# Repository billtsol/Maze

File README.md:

# Maze-Solving Robot

This project demonstrates how to use an Arduino board, IR sensors, and a motor driver shield to create a maze-solving robot. The robot is designed to navigate mazes by detecting, using sensors to make decisions at intersections.

## Requirements

To build this project, you will need the following components:

- ESP32 DevKit-S3
- IR sensors
- Motor driver shield
- Wheels and motors
- Jumper wires
- Battery pack
- Chassis
- Optional: Raspberry Pi (for additional functionality like 3D mapping and communication with a server)

## Circuit Diagram

## PCB

## Code

The code for this project is available in the `Maze.ino` file.

## Advanced Features

1. **Increased Size and Payload Capacity**: The robot's size can be increased to carry larger loads. This allows the robot to be used for more demanding applications, such as transporting packages or tools in industrial environments.

2. **Improved Navigation in Challenging Terrain**: The robot can be upgraded with enhanced drive systems to handle rough terrain. This feature enables the robot to navigate through more difficult environments, making it suitable for outdoor and emergency response applications.

3. **3D Mapping with LiDAR**: Adding LiDAR sensors to the robot allows it to create detailed 3D maps of its surroundings. This improves its maze-solving capabilities and makes it more versatile for tasks like underground exploration or hazardous area inspections. You can integrate LiDAR with software like ROS (Robot Operating System) and SLAM algorithms to create and visualize the 3D maps.

4. **Communication with Server using Raspberry Pi**: The robot can be connected to a server via a Raspberry Pi, enabling remote monitoring and control. This feature allows for real-time updates on the robot's progress through the maze and the ability to send and receive commands.

## Final Images

- Final pcb

- Final Mazo robot

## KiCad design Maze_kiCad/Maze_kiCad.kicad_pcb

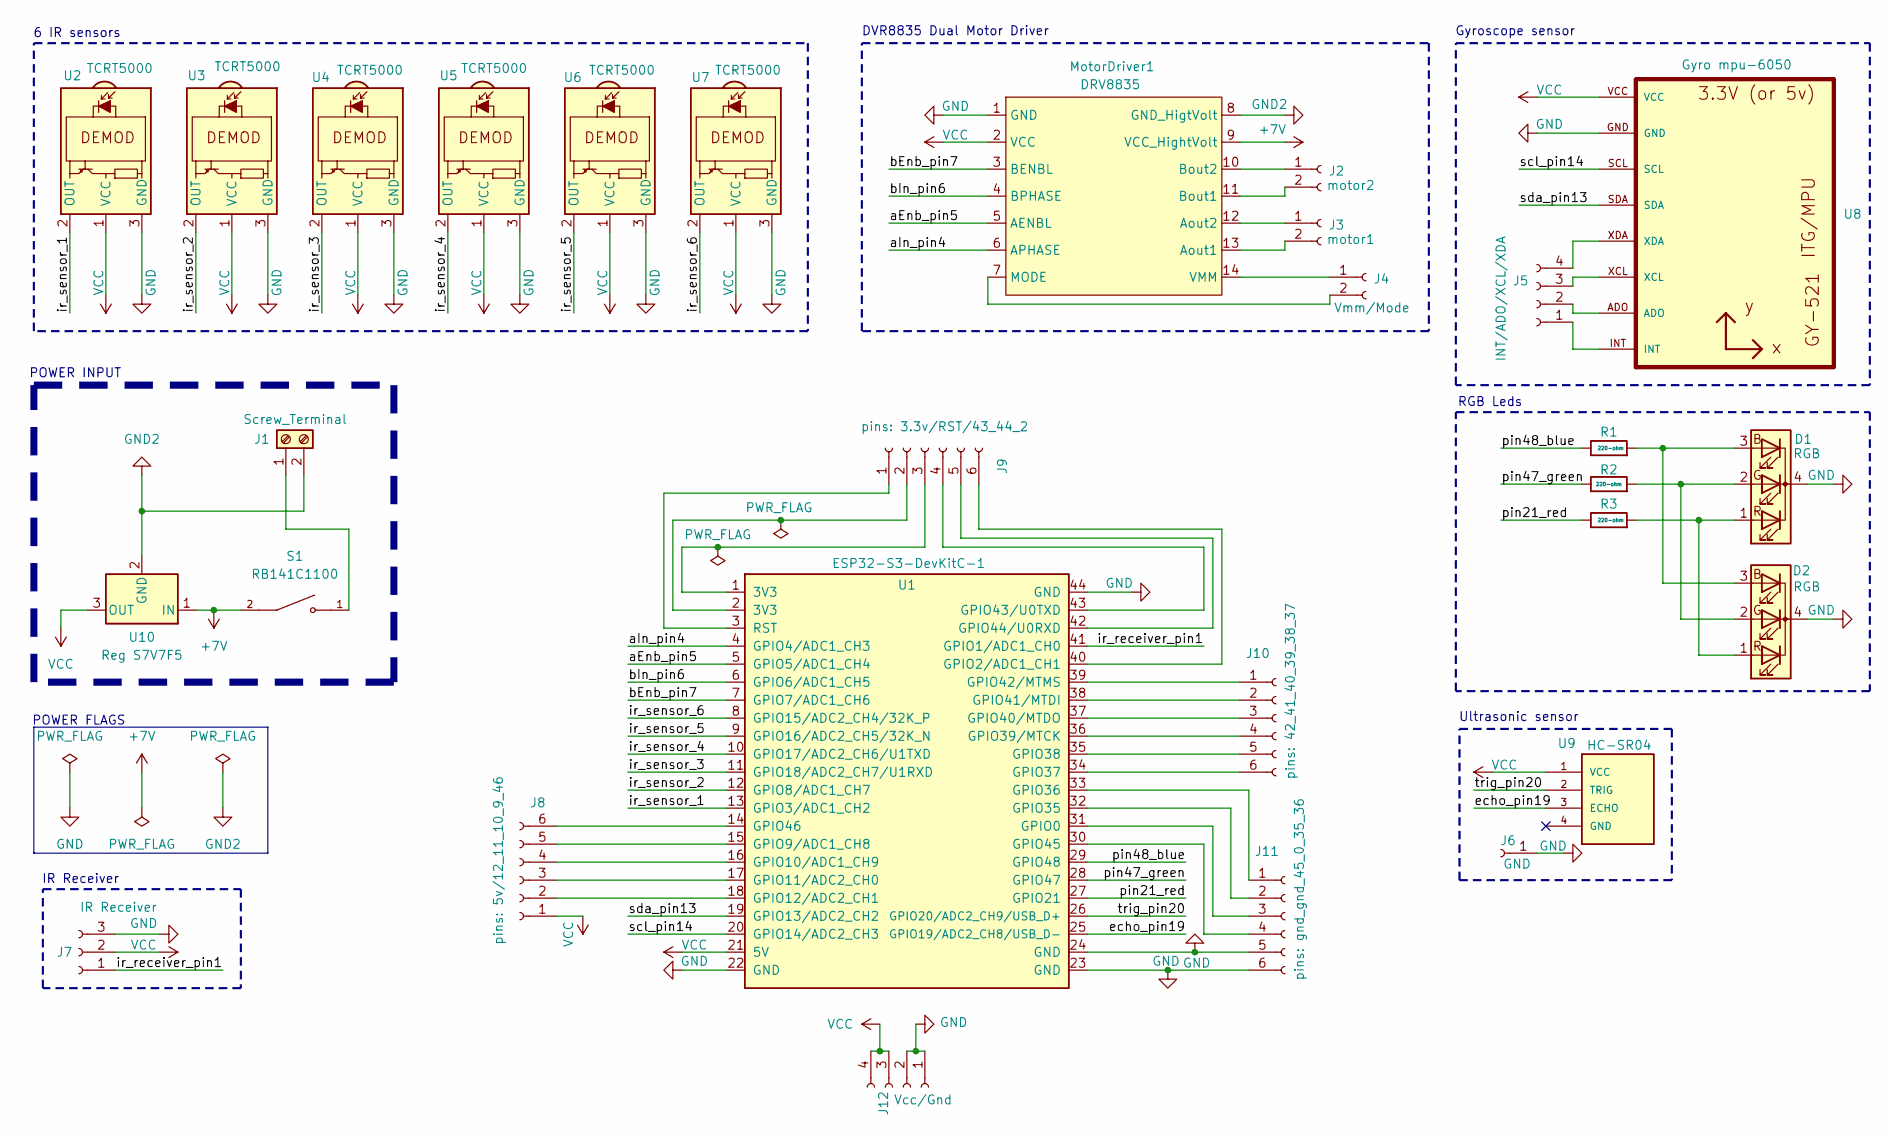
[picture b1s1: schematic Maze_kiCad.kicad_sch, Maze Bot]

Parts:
D1, D2: RGB; LED_D5.0mm-4_RGB_Staggered_Pins
J1: Screw_Terminal; TerminalBlock_Phoenix_MKDS-1,5-2_1x02_P5.00mm_Horizontal
J2: motor2; PinSocket_1x02_P2.54mm_Vertical
J3: motor1; PinSocket_1x02_P2.54mm_Vertical
J4: Vmm/Mode; PinSocket_1x02_P2.54mm_Vertical
J5: INT/ADO/XCL/XDA; PinSocket_1x04_P2.54mm_Vertical
J6: GND; PinSocket_1x01_P2.54mm_Vertical
J7: IR Receiver; PinSocket_1x03_P2.54mm_Vertical
J8: pins: 5v/12_11_10_9_46; PinSocket_1x06_P2.54mm_Vertical
J9: pins: 3.3v/RST/43_44_2; PinSocket_1x06_P2.54mm_Vertical
J10: pins: 42_41_40_39_38_37; PinSocket_1x06_P2.54mm_Vertical
J11: pins: gnd_gnd_45_0_35_36; PinSocket_1x06_P2.54mm_Vertical
J12: Vcc/Gnd; PinSocket_1x04_P2.54mm_Vertical
MotorDriver1: DRV8835; drv8835
R1, R2, R3: 220-ohm; R_Axial_DIN0204_L3.6mm_D1.6mm_P7.62mm_Horizontal
S1: RB141C1100; SW_RB141C1100; PARTREV C
U1: ESP32-S3-DevKitC-1; ESP32-S2-DevKitC-1
U2, U3, U4, U5, U6, U7: TCRT5000; Vishay_MINICAST-3Pin
U8: Gyro mpu-6050; GY-521
U9: HC-SR04; XCVR_HC-SR04
U10: Reg S7V7F5; PinSocket_1x03_P2.54mm_Vertical

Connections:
+7V: MotorDriver1.9 (VCC_HightVolt), S1.2, U10.1 (IN)
/aEnb_pin5: MotorDriver1.5 (AENBL), U1.5 (GPIO5/ADC1_CH4)
/aIn_pin4: MotorDriver1.6 (APHASE), U1.4 (GPIO4/ADC1_CH3)
/bEnb_pin7: MotorDriver1.3 (BENBL), U1.7 (GPIO7/ADC1_CH6)
/bIn_pin6: MotorDriver1.4 (BPHASE), U1.6 (GPIO6/ADC1_CH5)
/echo_pin19: U1.25 (GPIO19/ADC2_CH8/USB_D-), U9.3 (ECHO)
/ir_receiver_pin1: J7.1, U1.41 (GPIO1/ADC1_CH0)
/ir_sensor_1: U1.13 (GPIO3/ADC1_CH2), U2.2 (OUT)
/ir_sensor_2: U1.12 (GPIO8/ADC1_CH7), U3.2 (OUT)
/ir_sensor_3: U1.11 (GPIO18/ADC2_CH7/U1RXD), U4.2 (OUT)
/ir_sensor_4: U1.10 (GPIO17/ADC2_CH6/U1TXD), U5.2 (OUT)
/ir_sensor_5: U1.9 (GPIO16/ADC2_CH5/32K_N), U6.2 (OUT)
/ir_sensor_6: U1.8 (GPIO15/ADC2_CH4/32K_P), U7.2 (OUT)
/pin21_red: R3.1, U1.27 (GPIO21)
/pin47_green: R2.1, U1.28 (GPIO47)
/pin48_blue: R1.1, U1.29 (GPIO48)
/scl_pin14: U1.20 (GPIO14/ADC2_CH3), U8.SCL
/sda_pin13: U1.19 (GPIO13/ADC2_CH2), U8.SDA
/trig_pin20: U1.26 (GPIO20/ADC2_CH9/USB_D+), U9.2 (TRIG)
GND: D1.4 (K), D2.4 (K), J6.1, J7.3, J11.5, J11.6, J12.1, J12.2, MotorDriver1.1 (GND), U1.22 (GND), U1.23 (GND), U1.24 (GND), U1.44 (GND), U2.3 (GND), U3.3 (GND), U4.3 (GND), U5.3 (GND), U6.3 (GND), U7.3 (GND), U8.GND
GND2: J1.2, MotorDriver1.8 (GND_HigtVolt), U10.2 (GND)
unnamed: D1.3 (BA), D2.3 (BA), R1.2
unnamed: D1.2 (GA), D2.2 (GA), R2.2
unnamed: D1.1 (RA), D2.1 (RA), R3.2
unnamed: J1.1, S1.1
unnamed: J2.1, MotorDriver1.10 (Bout2)
unnamed: J2.2, MotorDriver1.11 (Bout1)
unnamed: J3.1, MotorDriver1.12 (Aout2)
unnamed: J3.2, MotorDriver1.13 (Aout1)
unnamed: J4.1, MotorDriver1.14 (VMM)
unnamed: J4.2, MotorDriver1.7 (MODE)
unnamed: J5.1, U8.INT
unnamed: J5.2, U8.ADO
unnamed: J5.3, U8.XCL
unnamed: J5.4, U8.XDA
unnamed: J8.2, U1.18 (GPIO12/ADC2_CH1)
unnamed: J8.3, U1.17 (GPIO11/ADC2_CH0)
unnamed: J8.4, U1.16 (GPIO10/ADC1_CH9)
unnamed: J8.5, U1.15 (GPIO9/ADC1_CH8)
unnamed: J8.6, U1.14 (GPIO46)
unnamed: J9.1, U1.3 (RST)
unnamed: J9.2, U1.2 (3V3)
unnamed: J9.3, U1.1 (3V3)
unnamed: J9.4, U1.43 (GPIO43/U0TXD)
unnamed: J9.5, U1.42 (GPIO44/U0RXD)
unnamed: J9.6, U1.40 (GPIO2/ADC1_CH1)
unnamed: J10.1, U1.39 (GPIO42/MTMS)
unnamed: J10.2, U1.38 (GPIO41/MTDI)
unnamed: J10.3, U1.37 (GPIO40/MTDO)
unnamed: J10.4, U1.36 (GPIO39/MTCK)
unnamed: J10.5, U1.35 (GPIO38)
unnamed: J10.6, U1.34 (GPIO37)
unnamed: J11.1, U1.33 (GPIO36)
unnamed: J11.2, U1.32 (GPIO35)
unnamed: J11.3, U1.31 (GPIO0)
unnamed: J11.4, U1.30 (GPIO45)
VCC: J7.2, J8.1, J12.3, J12.4, MotorDriver1.2 (VCC), U1.21 (5V), U2.1 (VCC), U3.1 (VCC), U4.1 (VCC), U5.1 (VCC), U6.1 (VCC), U7.1 (VCC), U8.VCC, U9.1 (VCC), U10.3 (OUT)

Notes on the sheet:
DVR8835 Dual Motor Driver
POWER FLAGS
Gyroscope sensor
RGB Leds
POWER INPUT
IR Receiver
6 IR sensors
Ultrasonic sensor

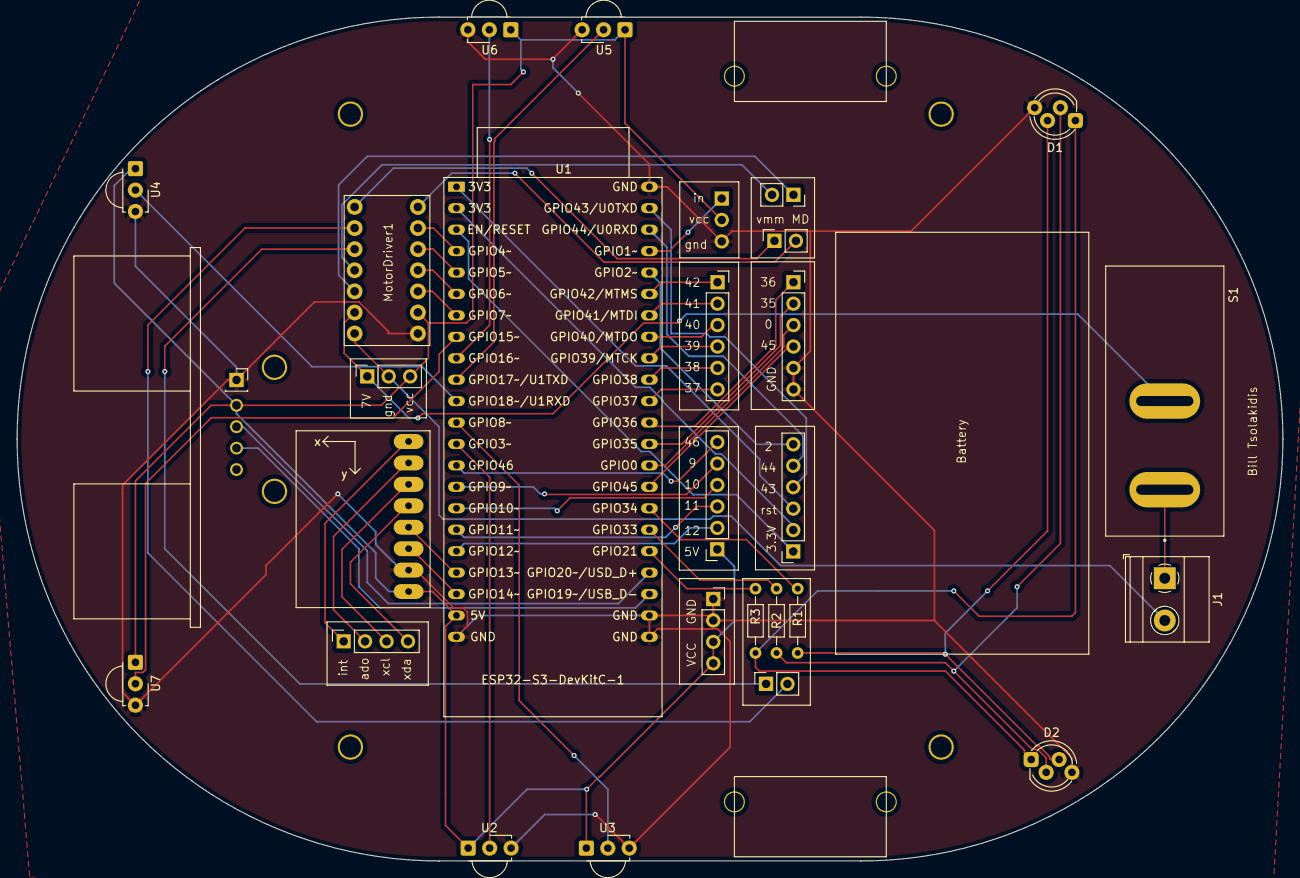
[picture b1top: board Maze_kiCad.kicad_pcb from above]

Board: 2 copper layers, 150.0 x 100.0 mm, 29 parts (1 on the bottom side), 57 nets.

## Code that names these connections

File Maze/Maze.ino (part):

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#define MOTOR_RIGHT_B_ENABLE_PIN 7 // Ορισμός του pin ενεργοποίησης του δεξιού κινητήρα

// Ορισμός των pins για τους αισθητήρες υπερύθρων (IR)
#define IR_SENSOR_1 3  // Αριστερός αισθητήρας
#define IR_SENSOR_2 8  // Αριστερός αισθητήρας
#define IR_SENSOR_3 15 // Κεντρικός αισθητήρας
#define IR_SENSOR_4 16 // Δεξιός αισθητήρας
#define IR_SENSOR_5 17 // Δεξιός αισθητήρας
#define IR_SENSOR_6 18 // Κεντρικός αισθητήρας

/* ********** Συμπερίληψη των απαραίτητων μεταβλητών ********** */
Adafruit_NeoPixel pixels(1, BUILDIN_RGB_LED_PIN, NEO_GRB + NEO_KHZ800); // Ορισμός του ενσωματωμένου RGB LED
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
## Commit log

2024-06-13 Build in rgb led
2024-06-14 ir receiver example code
2024-06-15 wifi commuication - change led color
2024-06-16 Start kicad - include esp32
2024-06-17 distance sensor example code
2024-06-18 Camera web server example code.
2024-06-20 Add ir sensor
2024-06-21 gyroscope example code
2024-06-22 add gyroscope symbol-footprint
2024-06-23 Drv 88333, example code
2024-06-24 drv8835 motor driver symnol and footprint
2024-06-25 add ultra sonic symbol and footprint
2024-06-26 Create all power inputs flags (5v and 7.4volt).
2024-06-27 Create all connections for 6 ir sensors and esp32-s3
2024-06-28 Make all connections for drv8835, esp32-s3 and motors inputs
2024-06-29 Create connections for gyroscope and ultrasonic sensor with esp32-s3
2024-06-29 Complete electric rule check!
2024-07-01 Example code for rgb leds
2024-07-02 Add two RGB LEDs to the circuit schematic
2024-07-02 Change schematic colors and print image.
2024-07-03 Remove the resistors because the two LEDs use the same pins
2024-07-04 Create version 1 of pcb
2024-07-05 Include all libraries and define all pins
2024-07-08 assign footprints
2024-07-12 Final maze robot pcb
2024-07-13 pcb images
2024-07-14 Change wifi password
2024-07-16 Final maze robot pcb and gerber files
2024-07-17 esp32 cam code, for openCV
2024-07-17 add readme.md
2024-07-18 Add code for server communication. Include the final image of the robot.
2024-07-19 image recognition with python openCV and yoloV3
2024-07-20 Implement basic Node.js server for real-time data reading
2024-07-21 gitignore file
2024-08-03 upgrade 3d models
2024-08-04 add comments for esp32cam
2024-08-05 image_recognition code upgrade
2024-08-06 upgrade gitignore
2024-08-07 Final kicad files
2024-08-08 rewrite comments
2024-08-09 python live video with yolo
2024-08-10 Frontend code - visualazation A* and 2d maze map
2024-08-11 back end code. get 20x20 maze map from esp32
2024-08-12 add functionality (explore map, A*, find path)
2024-08-13 Maze.ino - Add comments
2024-08-14 final maze code
2024-08-15 Short code explanation
2024-08-16 Add comments to the code
2024-08-17 Final robot images
2024-08-26 remove image
